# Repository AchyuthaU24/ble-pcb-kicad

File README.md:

# ble-pcb-kicad
BLE module PCB designed in KiCad - schematic, layout and BOM
# BLE PCB — KiCad

A custom BLE module PCB designed from scratch in KiCad 10.

## Overview
Designed a custom 2-layer IoT sensor PCB in KiCad 10 using the ESP32-C3-WROOM-02, featuring onboard power regulation, RF-compliant layout, and reliable boot/reset circuitry.

Validated the design through ERC, DRC, and 3D mechanical checks, producing fabrication-ready Gerber files for low-power wireless sensing applications.

## Schematic

## PCB 3D View

## PCB routing

## Tools
- KiCad 10
- [ESP32-C3-WROOM-02 — Main microcontroller and wireless communication module

LM2985S-3.3  — Power regulation from 9V to 3.3V

SB120 Schottky Diode — Reverse-current protection and improved efficiency]

## Author
Achyutha U | EEE, BNMIT 2027

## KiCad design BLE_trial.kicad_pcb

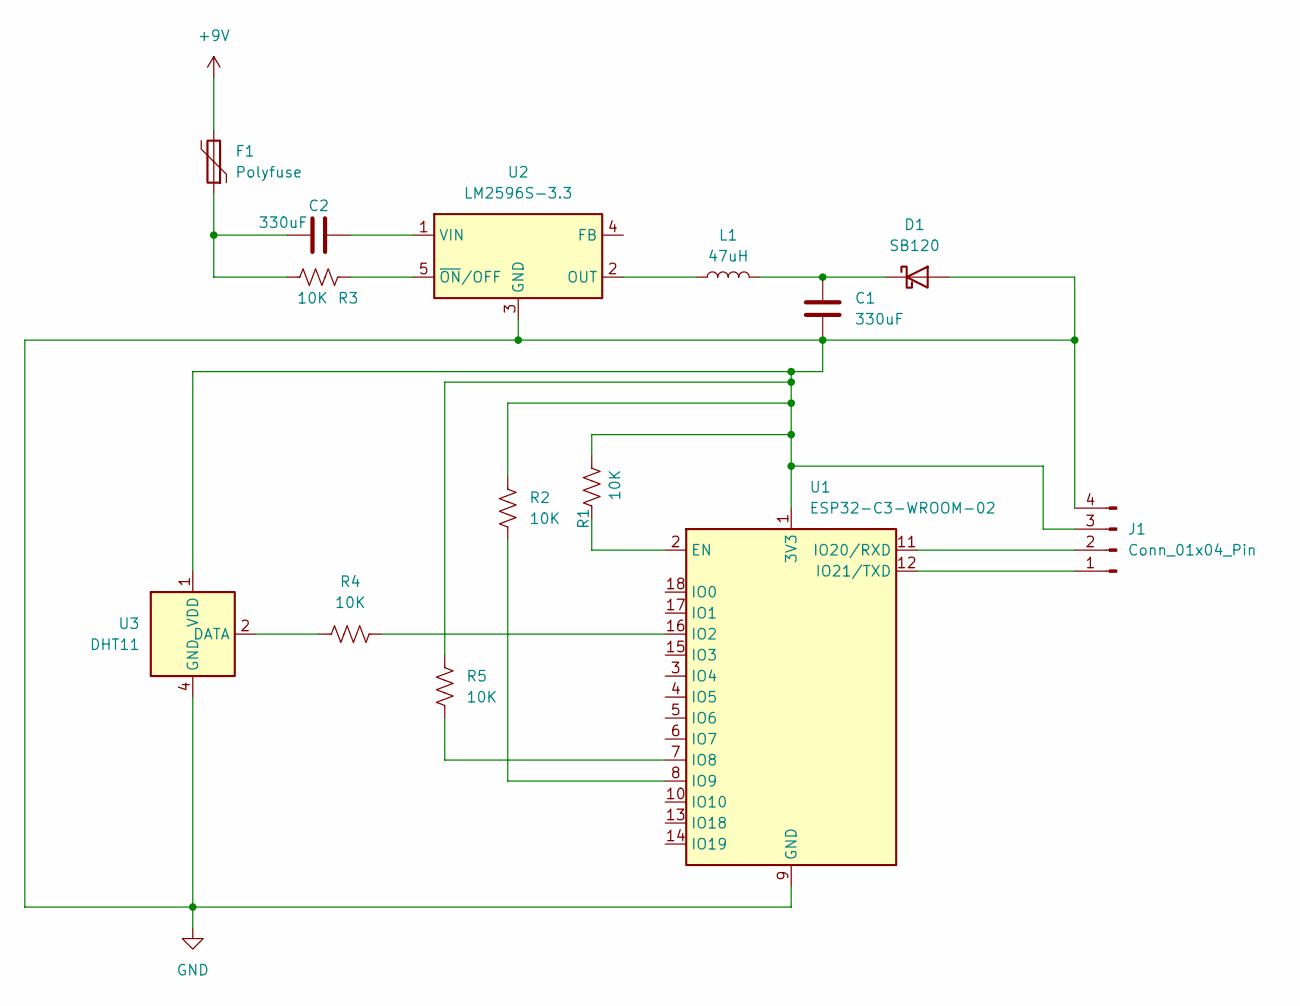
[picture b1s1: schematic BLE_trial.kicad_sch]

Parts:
C1, C2: 330uF; C_0805_2012Metric
D1: SB120; D_DO-41_SOD81_P10.16mm_Horizontal
F1: Polyfuse
J1: Conn_01x04_Pin; Wuerth_WR-WTB_64800411622_1x04_P1.50mm_Vertical
L1: 47uH; L_Radial_D10.0mm_P5.00mm_Fastron_07P
R1, R2, R3, R4, R5: 10K; R_Axial_DIN0204_L3.6mm_D1.6mm_P5.08mm_Horizontal
U1: ESP32-C3-WROOM-02
U2: LM2596S-3.3; TO-263-5_TabPin3
U3: DHT11; Aosong_DHT11_5.5x12.0_P2.54mm

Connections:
GND: C1.2, D1.2 (A), J1.3, J1.4, R1.2, R2.2, R5.1, U1.1 (3V3), U1.9 (GND), U1.19 (GND), U2.3 (GND), U3.1 (VDD), U3.4 (GND)
unnamed: C2.1, F1.1, R3.1
unnamed: C1.1, D1.1 (K), L1.2
unnamed: J1.1, U1.12 (IO21/TXD)
unnamed: J1.2, U1.11 (IO20/RXD)
unnamed: R1.1, U1.2 (EN)
unnamed: R4.2, U1.16 (IO2)
unnamed: R5.2, U1.7 (IO8)
unnamed: R2.1, U1.8 (IO9)
unnamed: L1.1, U2.2 (OUT)
unnamed: C2.2, U2.1 (VIN)
unnamed: R3.2, U2.5 (~ON/OFF)
unnamed: R4.1, U3.2 (DATA)

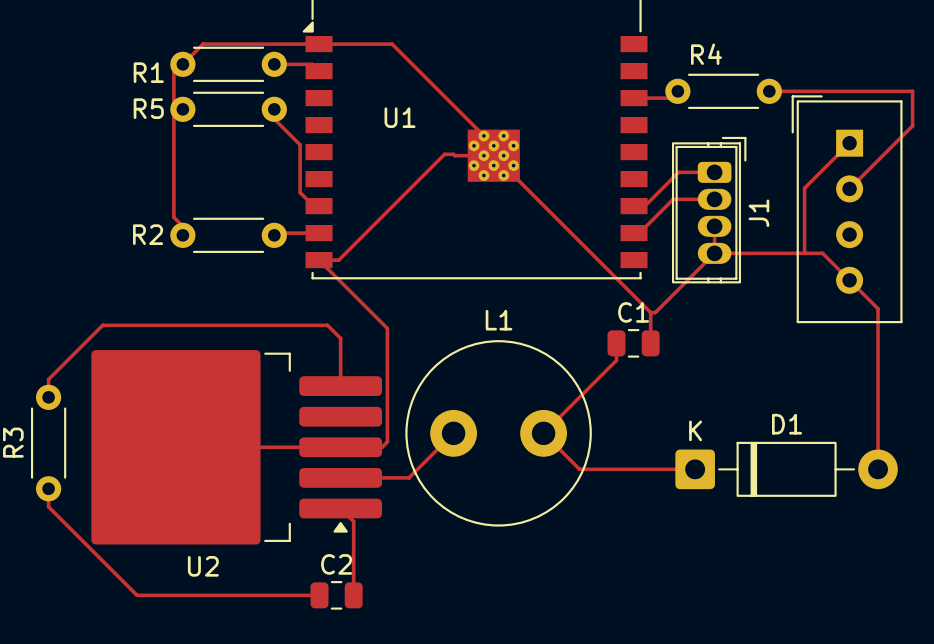
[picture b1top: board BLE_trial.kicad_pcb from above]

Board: 2 copper layers, 13 parts (0 on the bottom side), 13 nets.
